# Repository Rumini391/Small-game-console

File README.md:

# Small-game-console
A small game console with a joystick and a button and a display with some retro 2d games

This project includes the hardware design (PCB)

## Hardwares
- Seeed Studio XIAO ESP32-C3
- DIYTZT 1.5" 1.5 inch Full Color OLED Screen LCD LED Display Module 128x128 SPI Serial Port Interface SSD1351 Controller 128*128
- Alps Variable Resistance Type Multi Function Operating Device Stick Controller Rkjxk / Rkjxv Series RKJXV1224005
- 3.7V 1200mAh Lipo Lithium Polymer Rechargeable Battery 703450
- Kailh Choc Low Profile Switch 1350
- EG1271A switch

## Software
- Written in C++ (Arduino framework)

Example games:
- Snake
- Pong

(I added a boilerplate code in the SOFTWARE CODE folder, I will code the games when I can test them with the xiao when it's phisically here)

## Case
I designed the 3D model of the case in FreeCad, it is made of 2 bodies, the bottom and the top

## Photos

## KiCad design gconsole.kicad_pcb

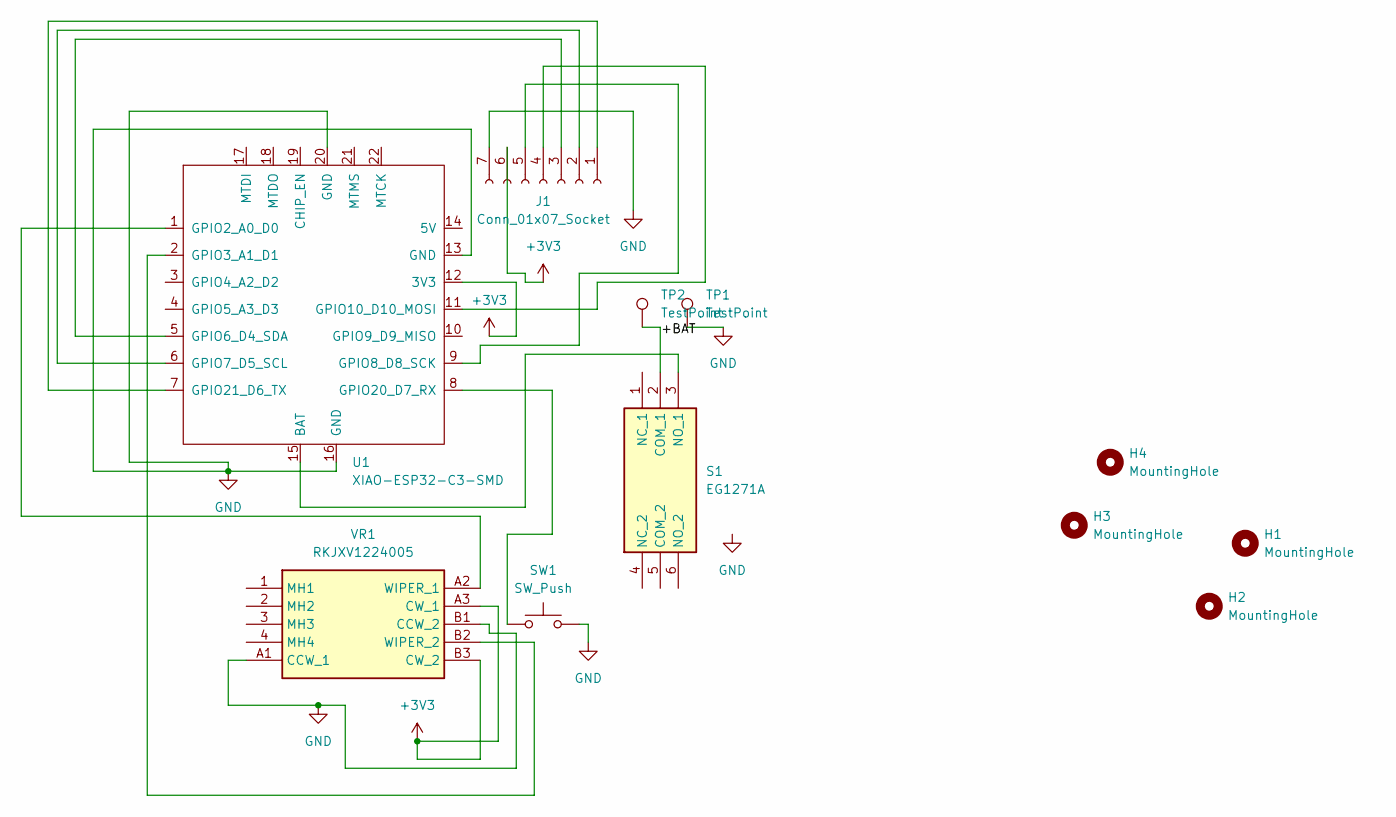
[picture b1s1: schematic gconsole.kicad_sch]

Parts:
H1, H2, H3, H4: MountingHole; MountingHole_3.2mm_M3
J1: Conn_01x07_Socket; PinHeader_1x07_P2.54mm_Vertical
S1: EG1271A; EG1271; Manufacturer_Part_Number EG1271A; Mouser Part Number 612-EG1271A
SW1: SW_Push; SW_choc_v1_1u
TP1, TP2: TestPoint; TestPoint_Pad_D4.0mm
U1: XIAO-ESP32-C3-SMD; XIAO-ESP32C3-SMD-modified
VR1: RKJXV1224005; Manufacturer_Part_Number RKJXV1224005; Mouser Part Number 688-RKJXV1224005

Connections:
+3V3: J1.6, U1.12 (3V3), VR1.A3 (CW_1), VR1.B3 (CW_2)
/+BAT: S1.2 (COM_1), TP2.1
GND: J1.7, SW1.2, TP1.1, U1.13 (GND), U1.16 (GND), U1.20 (GND), VR1.A1 (CCW_1), VR1.B1 (CCW_2)
unnamed: J1.1, U1.7 (GPIO21_D6_TX)
unnamed: J1.2, U1.6 (GPIO7_D5_SCL)
unnamed: J1.3, U1.5 (GPIO6_D4_SDA)
unnamed: J1.4, U1.11 (GPIO10_D10_MOSI)
unnamed: J1.5, U1.9 (GPIO8_D8_SCK)
unnamed: S1.3 (NO_1), U1.15 (BAT)
unnamed: U1.1 (GPIO2_A0_D0), VR1.A2 (WIPER_1)
unnamed: U1.2 (GPIO3_A1_D1), VR1.B2 (WIPER_2)
unnamed: SW1.1, U1.8 (GPIO20_D7_RX)

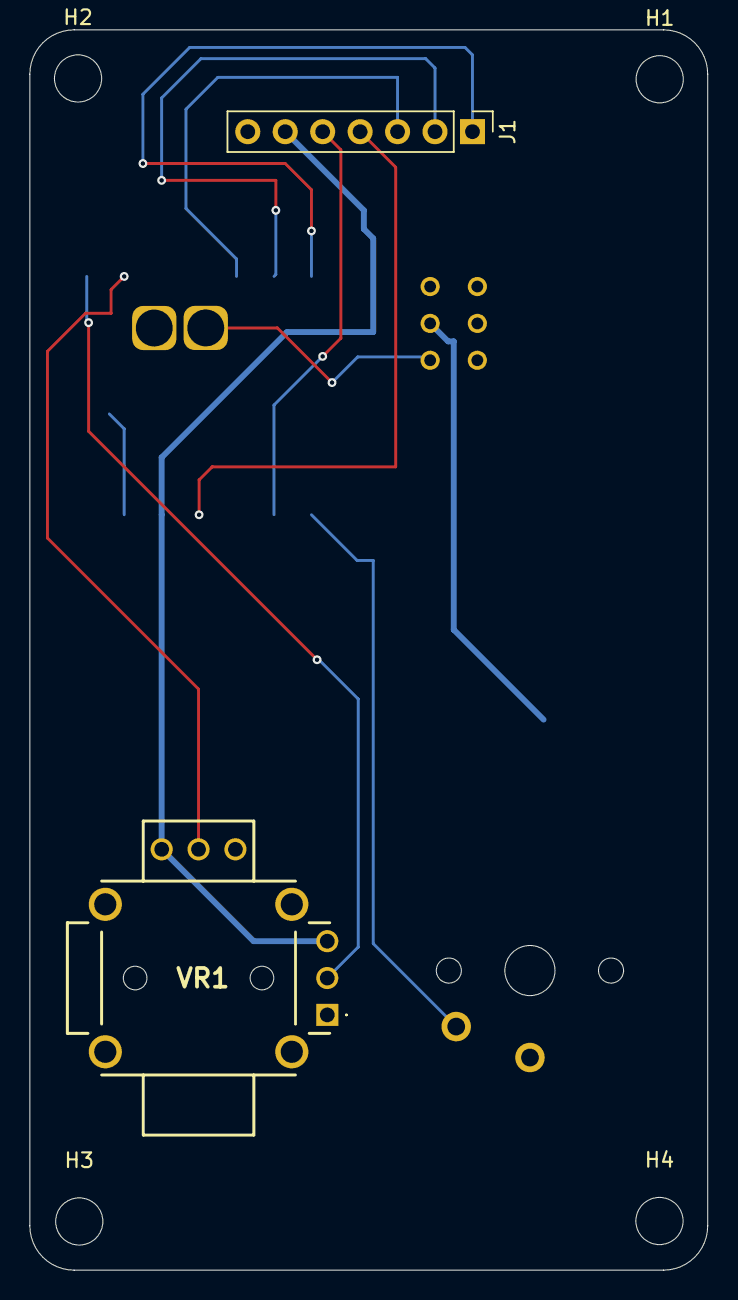
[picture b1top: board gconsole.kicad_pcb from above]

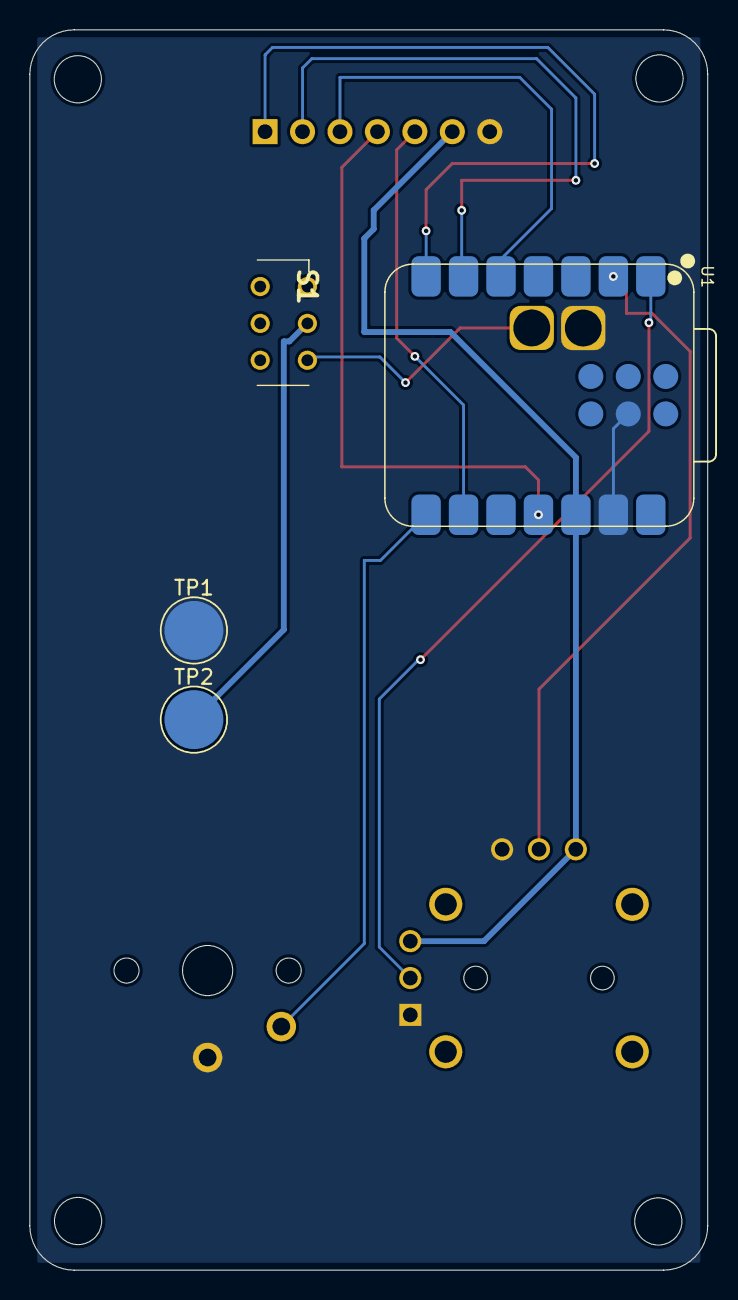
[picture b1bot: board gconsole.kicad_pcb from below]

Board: 2 copper layers, 46.0 x 84.1 mm, 11 parts (4 on the bottom side), 12 nets.

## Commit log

2025-10-10 Started pcb
    Imported libraries and started designing pcb
2025-10-11 Imported modules in KiCad
2025-10-12 Finished designing PCB
2025-10-12 Added example software code
2025-10-12 added bom.csv
2025-10-12 Finished PCB + added software code + updated README + added bom.csv
2025-10-13 updated bom.csv
2025-10-24 Designed case
2025-10-24 updated bom
